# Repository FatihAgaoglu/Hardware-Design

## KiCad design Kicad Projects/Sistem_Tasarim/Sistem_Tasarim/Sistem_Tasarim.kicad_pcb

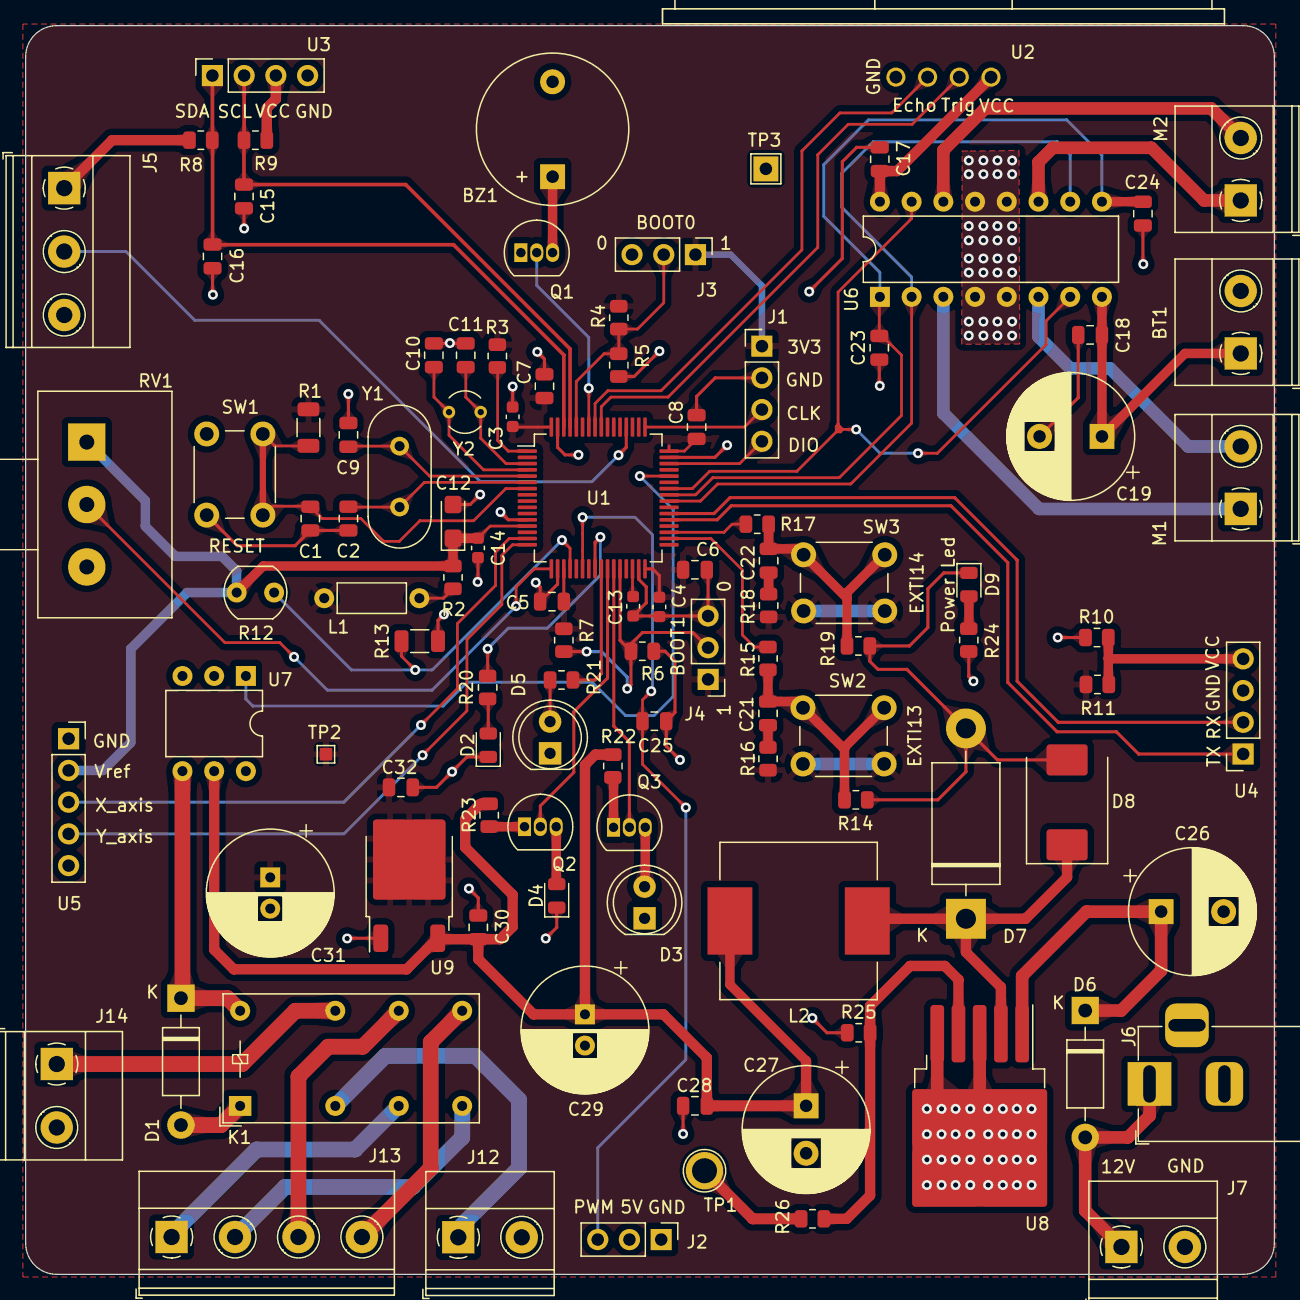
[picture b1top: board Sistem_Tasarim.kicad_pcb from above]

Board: 4 copper layers, 100.0 x 100.0 mm, 104 parts (0 on the bottom side), 68 nets.

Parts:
BT1: Battery; TerminalBlock_Phoenix_MKDS-1,5-2_1x02_P5.00mm_Horizontal
BZ1: Buzzer; Buzzer_12x9.5RM7.6
C1, C5, C6, C7, C8, C15, C16, C17, C18, C21, C22, C23, C24, C25, C28: 100nF; C_0805_2012Metric
C2, C9: 22pF; C_0805_2012Metric
C3, C4, C14: 100nF; C_0603_1608Metric
C10, C11: 6.8pF; C_0805_2012Metric
C12: 1uF; CP_EIA-3216-18_Kemet-A
C13: 2.2uF; C_0603_1608Metric
C19: 1000uF; CP_Radial_D10.0mm_P5.00mm
C26: 680uF; CP_Radial_D10.0mm_P5.00mm
C27: 220uF; CP_Radial_D10.0mm_P3.80mm
C29, C31: 10uF; CP_Radial_D10.0mm_P2.50mm
C30, C32: 1uF; C_0805_2012Metric
D1, D6: 1N4007; D_DO-41_SOD81_P10.16mm_Horizontal
D2, D4, D9: LED; LED_0805_2012Metric
D3, D5: LED; LED_D5.0mm
D7: 1N5822; D_DO-201AD_P15.24mm_Horizontal
D8: SS34; D_SMC
J1: Prog_Conn_01x04; PinHeader_1x04_P2.54mm_Vertical
J2, J3, J4: Conn_01x03; PinHeader_1x03_P2.54mm_Vertical
J5: Screw_Terminal_01x03; TerminalBlock_Phoenix_MKDS-1,5-3-5.08_1x03_P5.08mm_Horizont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
J6: Barrel_Jack_Switch_Pin3Ring; DC_Power_Jack
J7, J12, J14: Screw_Terminal_01x02; TerminalBlock_Phoenix_MKDS-1,5-2-5.08_1x02_P5.08mm_Horizont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
J13: Screw_Terminal_01x04; TerminalBlock_Phoenix_MKDS-1,5-4-5.08_1x04_P5.08mm_Horizont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
K1: AZ850-x; Relay_DPDT_Finder_30.22
L1: 100uH; L_Axial_L5.3mm_D2.2mm_P7.62mm_Horizontal_Vishay_IM-1
L2: 33uH; INDUCTOR_12x12x8
M1: Motor_DC_UST; TerminalBlock_Phoenix_MKDS-1,5-2_1x02_P5.00mm_Horizontal
M2: Motor_DC_ALT; TerminalBlock_Phoenix_MKDS-1,5-2_1x02_P5.00mm_Horizontal
Q1, Q2, Q3: BC547; TO-92_Inline
R1: 1K; R_1206_3216Metric
R2: 47R; R_0805_2012Metric
R3, R10, R11: 0R; R_0805_2012Metric
R4, R7: 10k; R_0805_2012Metric
R5, R6: 510R; R_0805_2012Metric
R8, R9: 4.7K; R_0805_2012Metric
R12: LDR03; R_LDR_5.0x4.1mm_P3mm_Vertical
R13: 10K; R_1206_3216Metric
R14, R19: 220K; R_0805_2012Metric
R15, R17: 330R; R_0805_2012Metric
R16, R18, R20, R21, R22, R23: 100R; R_0805_2012Metric
R24: 470R; R_0805_2012Metric
R25: 1K; R_0805_2012Metric
R26: 3K; R_0805_2012Metric
RV1: 100K; Potansiyometre
SW1, SW2, SW3: SW_MEC_5E; SW_PUSH_6mm_H4.3mm
TP1: 5V; TestPoint_Plated_Hole_D2.0mm
TP2: 3V3; TestPoint_Pad_1.0x1.0mm
TP3: GND; TestPoint_THTPad_2.0x2.0mm_Drill1.0mm
U1: STM32F401RCTx; LQFP-64_10x10mm_P0.5mm
U2: HC-SR04
U3: Oled_Display
U4: HC06 Bluetooth Sensor; HC06
U5: Joystick
U6: L293D; DIP-16_W7.62mm
U7: 4N25; DIP-6_W7.62mm
U8: LM2596S-5; TO-263-5_TabPin3
U9: LD1086DT33TR; TO-252-2
Y1: Crystal_8Mhz; Crystal_HC49-4H_Vertical
Y2: Crystal_32.768Khz; Crystal_AT310_D3.0mm_L10.0mm_Vertical

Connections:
+3V3: C3.1, C4.1, C5.1, C6.1, C7.1, C8.1, C31.1, C32.1, J1.1, J3.1, J4.1, L1.1, R1.1, R3.1, R4.1, R7.1, R11.2, R16.2, R18.2, SW2.1, SW2.2, SW3.1, SW3.2, TP2.1, U1.19 (VDD), U1.32 (VDD), U1.48 (VDD), U1.64 (VDD), U9.2 (OUT)
+5V: C17.2, C27.1, C28.1, C29.1, C30.1, J2.2, J5.1, L2.2, Q1.1 (C), R8.1, R9.1, R10.2, R22.1, R23.1, R24.1, R26.2, TP1.1, U2.1 (VCC), U3.3 (VCC), U6.16 (VCC1), U7.5, U9.3 (IN)
BOOT0: J3.2, R4.2, R5.1, U1.60 (BOOT0)
BOOT1: J4.2, R6.1, R7.2, U1.28 (PB2)
Buzzer_Output: Q1.2 (B), U1.58 (PB6)
DC_Engine_Left: U1.40 (PC9), U6.2 (1A), U6.10 (3A)
DC_Engine_PWM: C23.2, C24.2, U1.41 (PA8), U6.1 (EN1,2), U6.9 (EN3,4)
DC_Engine_Right: U1.42 (PA9), U6.7 (2A), U6.15 (4A)
Echo: U1.57 (PB5), U2.3 (ECHO)
GNDREF: BT1.2 (-), BZ1.2 (+), C1.1, C2.2, C3.2, C4.2, C5.2, C6.2, C7.2, C8.2, C9.2, C10.2, C11.2, C12.2, C13.1, C14.2, C15.2, C16.2, C17.1, C18.2, C19.2, C23.1, C24.1, C25.1, C26.2, C27.2, C28.2, C29.2, C30.2, C31.2, C32.2, D1.2 (A), D2.1 (K), D3.1 (K), D4.1 (K), D5.1 (K), D7.2 (A), D8.2 (A), D9.1 (K), J1.2, J2.1, J3.3, J4.3, J5.3, J6.2, J6.3, J7.2, K1.10, R5.2, R6.2, R13.2, R14.2, R19.2, R25.1, RV1.3, SW1.3 (K), SW1.4 (A), TP3.1, U1.12 (VSSA), U1.18 (VSS), U1.31 (VSS), U1.47 (VSS), U1.63 (VSS), U2.4 (GND), U3.4 (GND), U4.3 (GND), U5.1 (GND), U6.4 (GND), U6.5 (GND), U6.12 (GND), U6.13 (GND), U7.2, U8.3 (GND), U8.5 (~ON/OFF), U9.1 (ADJ/GND)
I2C_SCL: C15.1, R9.2, U1.61 (PB8), U3.2 (SCL)
I2C_SDA: C16.1, R8.2, U1.62 (PB9), U3.1 (SDA)
Interrupt_EXTI13: R15.1, U1.34 (PB13)
Interrupt_EXTI14: R17.1, U1.35 (PB14)
NRST: C1.2, R1.2, SW1.1, SW1.2, U1.7 (NRST)
unnamed: C26.1, D6.1 (K), U8.1 (VIN)
unnamed: R3.2, U1.1 (VBAT)
unnamed: R10.1, R11.1, U4.4 (VCC)
unnamed: BT1.1 (+), C18.1, C19.1, U6.8 (VCC2)
unnamed: BZ1.1 (-), Q1.3 (E)
unnamed: C21.2, R16.1
unnamed: C22.2, R18.1
unnamed: D1.1 (K), K1.1, U7.4
unnamed: D2.2 (A), R20.2
unnamed: D3.2 (A), Q3.3 (E)
unnamed: D4.2 (A), Q2.3 (E)
unnamed: D5.2 (A), R21.2
unnamed: D6.2 (A), J6.1, J7.1
unnamed: D7.1 (K), D8.1 (K), L2.1, U8.2 (OUT)
unnamed: D9.2 (A), R24.2
unnamed: J12.1, K1.3
unnamed: J13.1, K1.2
unnamed: J13.2, K1.4
unnamed: J13.3, K1.9
unnamed: J13.4, K1.7
unnamed: J14.1, K1.8
unnamed: L1.2, R2.1
unnamed: M1.1 (+), U6.3 (1Y)
unnamed: M1.2 (-), U6.6 (2Y)
unnamed: M2.1 (+), U6.11 (3Y)
unnamed: M2.2 (-), U6.14 (4Y)
unnamed: Q2.1 (C), R23.2
unnamed: Q3.1 (C), R22.2
unnamed: C21.1, R14.1, R15.2, SW2.3 (K), SW2.4 (A)
unnamed: C22.1, R17.2, R19.1, SW3.3 (K), SW3.4 (A)
unnamed: C13.2, U1.30 (VCAP1)
unnamed: R25.2, R26.1, U8.4 (FB)
PHOTO_ELECTRIC_SWITCH: J5.2, U1.52 (PC11)
RCC_OSC_HSE_1: C9.1, U1.5 (PH0), Y1.1
RCC_OSC_HSE_2: C2.1, U1.6 (PH1), Y1.2
RCC_OSC_LSE_1: C11.1, U1.3 (PC14), Y2.1
RCC_OSC_LSE_2: C10.1, U1.4 (PC15), Y2.2
Relay_Output: U1.44 (PA11), U7.1
SWCLK: J1.3, U1.49 (PA14)
SWDIO: J1.4, U1.46 (PA13)
Servo_Engine_PWM: C25.2, J2.3, U1.22 (PA6)
Trig: U1.56 (PB4), U2.2 (TRIG)
USART6_RX: U1.38 (PC7), U4.2 (TX)
USART6_TX: U1.37 (PC6), U4.1 (RX)
User_Led_0: R20.1, U1.24 (PC4)
User_Led_1: R21.1, U1.25 (PC5)
User_Led_2: Q2.2 (B), U1.26 (PB0)
User_Led_3: Q3.2 (B), U1.27 (PB1)
VREF+: C12.1, C14.1, R2.2, R12.1, RV1.1, U1.13 (VREF+), U5.2 (5V)
X_axis: U1.15 (PA1), U5.3 (VRX)
Y_axis: U1.16 (PA2), U5.4 (VRY)
ldr_value: R12.2, R13.1, U1.20 (PA4)
pot_value: RV1.2, U1.17 (PA3)

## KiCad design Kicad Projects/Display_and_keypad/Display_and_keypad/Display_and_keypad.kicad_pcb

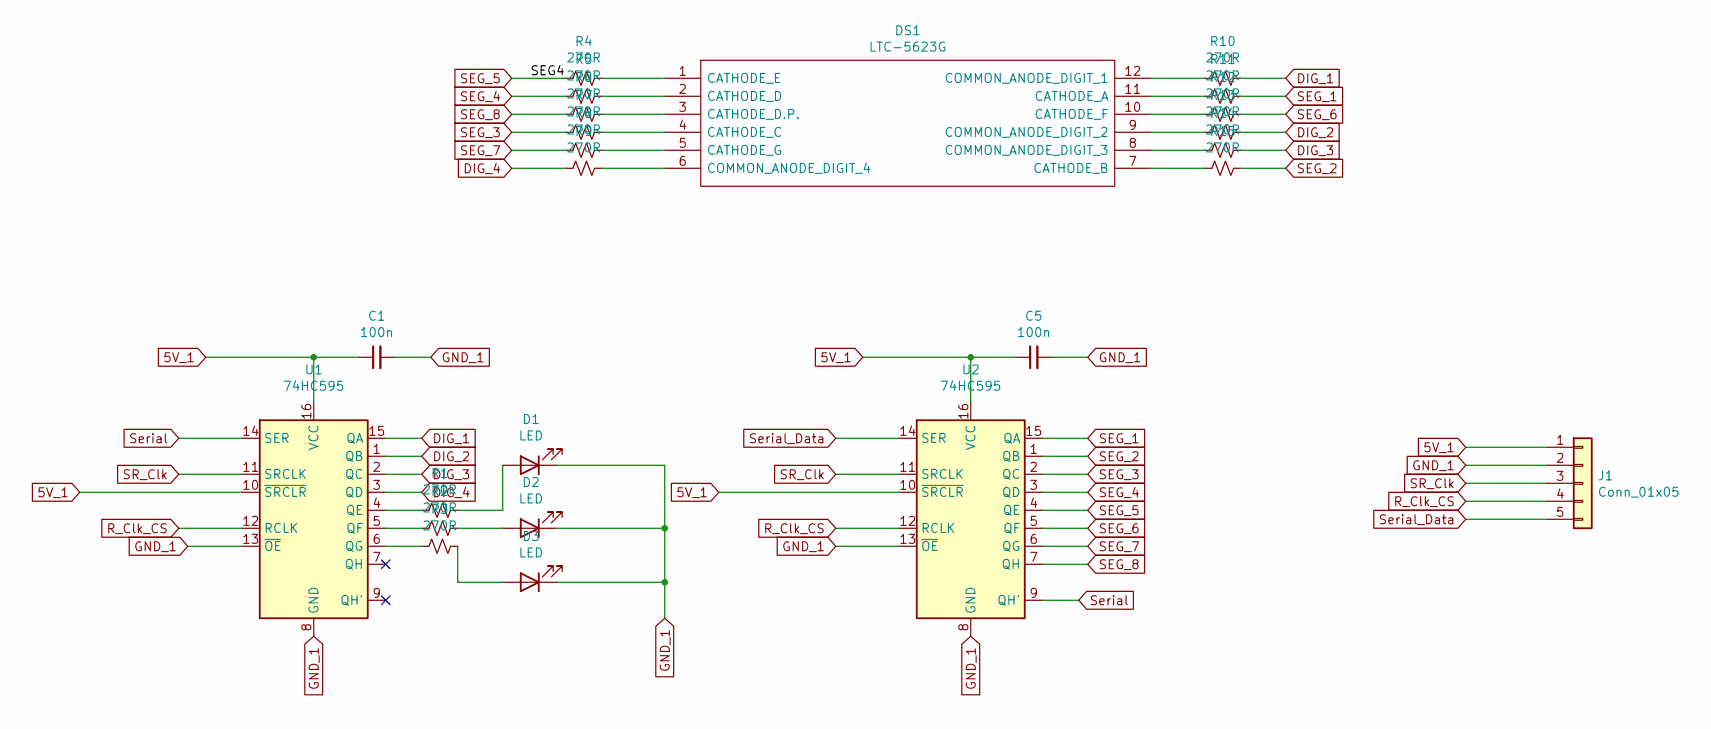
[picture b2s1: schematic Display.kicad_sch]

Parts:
C1, C5: 100n; C_0805_2012Metric_Pad1.18x1.45mm_HandSolder
D1, D2, D3: LED; LED_0805_2012Metric_Pad1.15x1.40mm_HandSolder
DS1: LTC-5623G; DIPS1524W75P254L5030H825Q12N
J1: Conn_01x05; PinHeader_1x05_P2.54mm_Vertical
R1, R2, R3, R4, R5, R6, R7, R8, R9, R10, R11, R12, R13, R14, R15: 270R; R_0805_2012Metric_Pad1.20x1.40mm_HandSolder
U1, U2: 74HC595; TSSOP-16_4.4x5mm_P0.65mm

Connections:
5V_1: C1.1, C5.1, J1.1, U1.10 (~SRCLR), U1.16 (VCC), U2.10 (~SRCLR), U2.16 (VCC)
DIG_1: R10.1, U1.15 (QA)
DIG_2: R13.1, U1.1 (QB)
DIG_3: R14.1, U1.2 (QC)
DIG_4: R9.2, U1.3 (QD)
GND_1: C1.2, C5.2, D1.1 (K), D2.1 (K), D3.1 (K), J1.2, U1.8 (GND), U1.13 (~OE), U2.8 (GND), U2.13 (~OE)
unnamed: D1.2 (A), R1.1
unnamed: D2.2 (A), R2.1
unnamed: D3.2 (A), R3.1
unnamed: DS1.1 (CATHODE_E), R4.1
unnamed: DS1.2 (CATHODE_D), R5.1
unnamed: DS1.3 (CATHODE_D.P.), R6.1
unnamed: DS1.4 (CATHODE_C), R7.1
unnamed: DS1.5 (CATHODE_G), R8.1
unnamed: DS1.6 (COMMON_ANODE_DIGIT_4), R9.1
unnamed: DS1.7 (CATHODE_B), R15.2
unnamed: DS1.8 (COMMON_ANODE_DIGIT_3), R14.2
unnamed: DS1.9 (COMMON_ANODE_DIGIT_2), R13.2
unnamed: DS1.10 (CATHODE_F), R12.2
unnamed: DS1.11 (CATHODE_A), R11.2
unnamed: DS1.12 (COMMON_ANODE_DIGIT_1), R10.2
unnamed: R1.2, U1.4 (QE)
unnamed: R2.2, U1.5 (QF)
unnamed: R3.2, U1.6 (QG)
R_Clk_CS: J1.4, U1.12 (RCLK), U2.12 (RCLK)
SEG_1: R11.1, U2.15 (QA)
SEG_2: R15.1, U2.1 (QB)
SEG_3: R7.2, U2.2 (QC)
SEG_4: R5.2, U2.3 (QD)
SEG_5: R4.2, U2.4 (QE)
SEG_6: R12.1, U2.5 (QF)
SEG_7: R8.2, U2.6 (QG)
SEG_8: R6.2, U2.7 (QH)
SR_Clk: J1.3, U1.11 (SRCLK), U2.11 (SRCLK)
Serial: U1.14 (SER), U2.9 (QH')
Serial_Data: J1.5, U2.14 (SER)

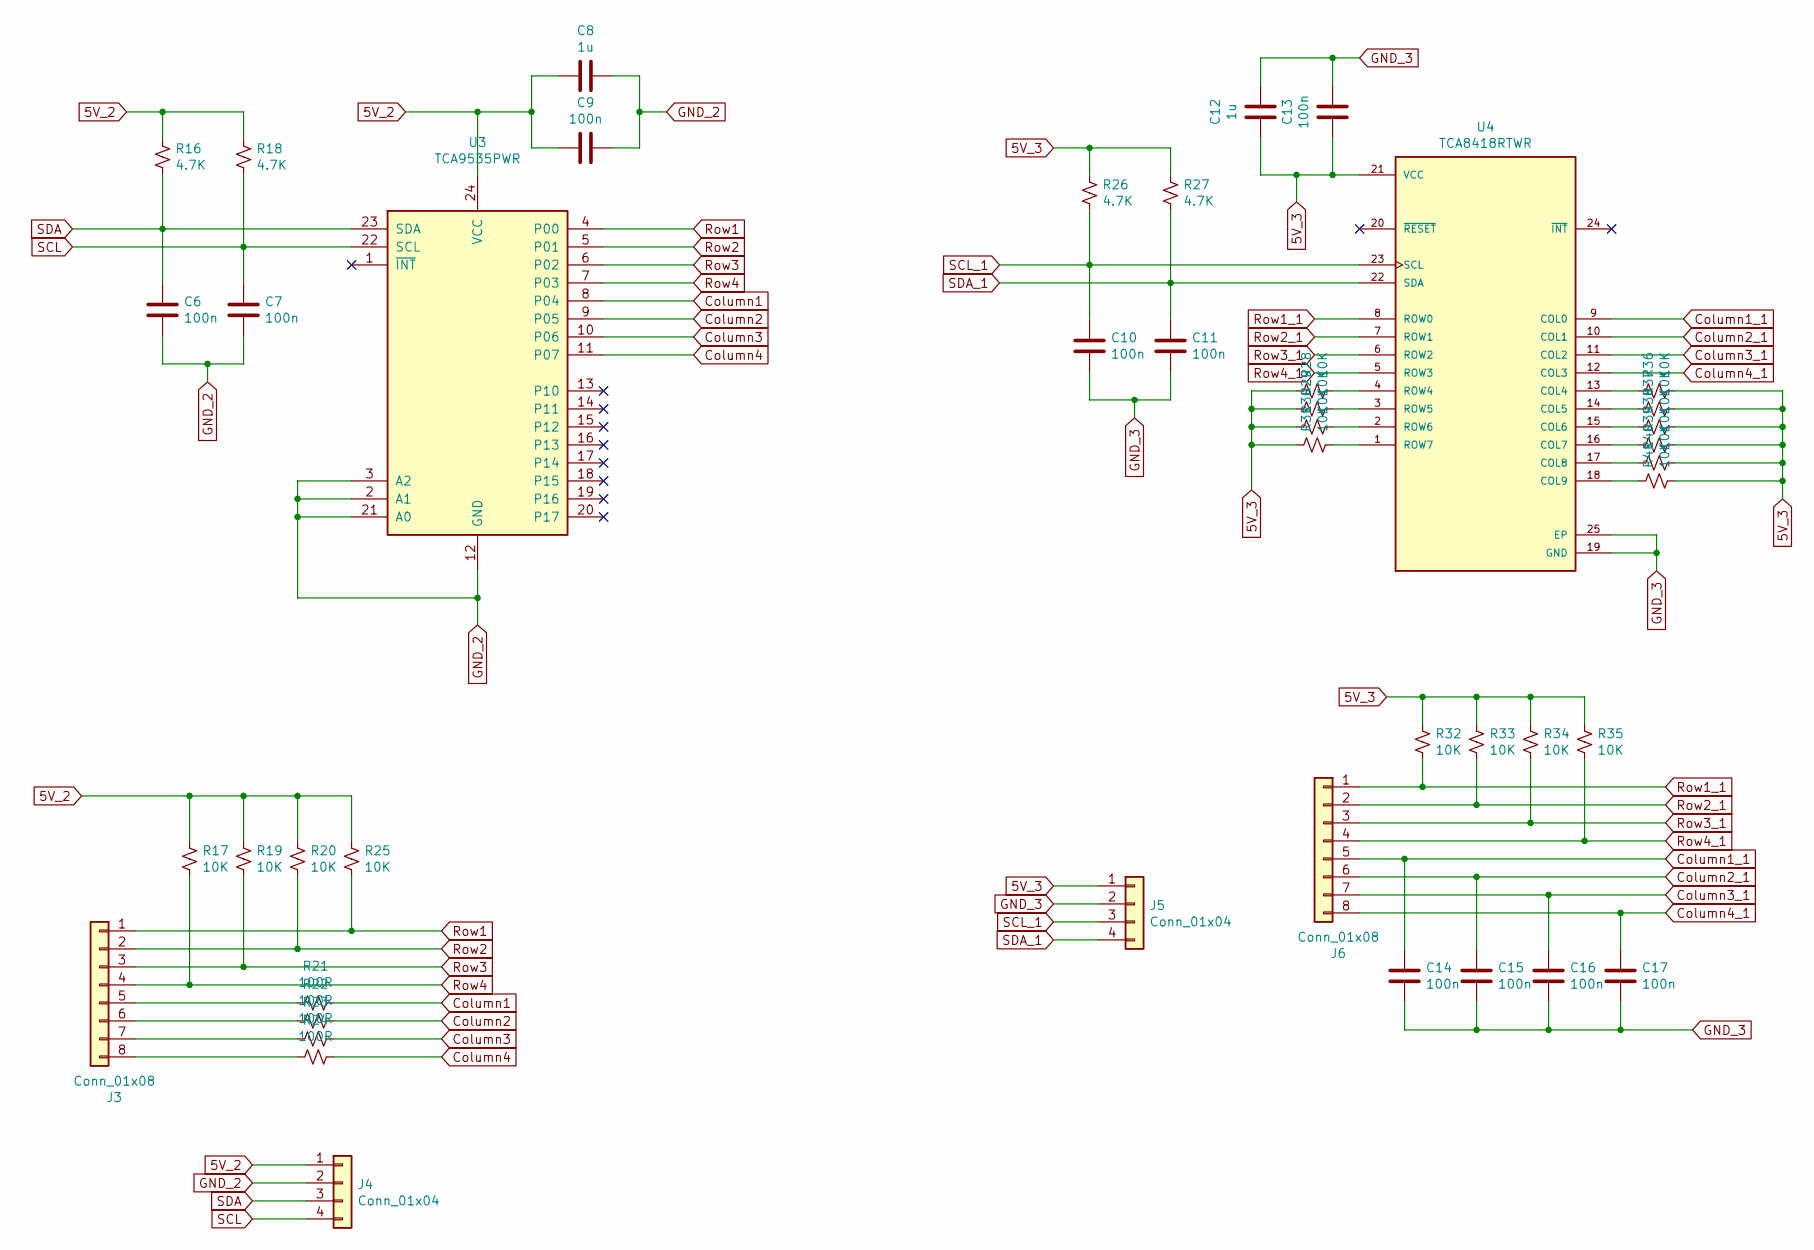
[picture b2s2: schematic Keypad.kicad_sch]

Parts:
C6, C7, C9, C10, C11, C13, C14, C15, C16, C17: 100n; C_0805_2012Metric_Pad1.18x1.45mm_HandSolder
C8, C12: 1u; C_0805_2012Metric_Pad1.18x1.45mm_HandSolder
J3, J6: Conn_01x08; PinHeader_1x08_P2.54mm_Vertical
J4, J5: Conn_01x04; PinHeader_1x04_P2.54mm_Vertical
R16, R18, R26, R27: 4.7K; R_0805_2012Metric_Pad1.20x1.40mm_HandSolder
R17, R19, R20, R25, R28, R29, R30, R31, R32, R33, R34, R35, R36, R37, R38, R39, R40, R41: 10K; R_0805_2012Metric_Pad1.20x1.40mm_HandSolder
R21, R22, R23, R24: 100R; R_0805_2012Metric_Pad1.20x1.40mm_HandSolder
U3: TCA9535PWR; TSSOP-24_4.4x7.8mm_P0.65mm
U4: TCA8418RTWR; QFN50P400X400X80-25N

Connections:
5V_2: C8.2, C9.2, J4.1, R16.1, R17.1, R18.1, R19.1, R20.1, R25.1, U3.24 (VCC)
5V_3: C12.2, C13.2, J5.1, R26.1, R27.1, R28.1, R29.1, R30.1, R31.1, R32.1, R33.1, R34.1, R35.1, R36.2, R37.2, R38.2, R39.2, R40.2, R41.2, U4.21 (VCC)
Column1: R21.1, U3.8 (P04)
Column1_1: C14.1, J6.5, U4.9 (COL0)
Column2: R22.1, U3.9 (P05)
Column2_1: C15.1, J6.6, U4.10 (COL1)
Column3: R23.1, U3.10 (P06)
Column3_1: C16.1, J6.7, U4.11 (COL2)
Column4: R24.1, U3.11 (P07)
Column4_1: C17.1, J6.8, U4.12 (COL3)
GND_2: C6.2, C7.2, C8.1, C9.1, J4.2, U3.2 (A1), U3.3 (A2), U3.12 (GND), U3.21 (A0)
GND_3: C10.2, C11.2, C12.1, C13.1, C14.2, C15.2, C16.2, C17.2, J5.2, U4.19 (GND), U4.25 (EP)
unnamed: J3.5, R21.2
unnamed: J3.6, R22.2
unnamed: J3.7, R23.2
unnamed: J3.8, R24.2
unnamed: R28.2, U4.4 (ROW4)
unnamed: R29.2, U4.3 (ROW5)
unnamed: R30.2, U4.2 (ROW6)
unnamed: R31.2, U4.1 (ROW7)
unnamed: R36.1, U4.13 (COL4)
unnamed: R37.1, U4.14 (COL5)
unnamed: R38.1, U4.15 (COL6)
unnamed: R39.1, U4.16 (COL7)
unnamed: R40.1, U4.17 (COL8)
unnamed: R41.1, U4.18 (COL9)
Row1: J3.1, R25.2, U3.4 (P00)
Row1_1: J6.1, R32.2, U4.8 (ROW0)
Row2: J3.2, R20.2, U3.5 (P01)
Row2_1: J6.2, R33.2, U4.7 (ROW1)
Row3: J3.3, R19.2, U3.6 (P02)
Row3_1: J6.3, R34.2, U4.6 (ROW2)
Row4: J3.4, R17.2, U3.7 (P03)
Row4_1: J6.4, R35.2, U4.5 (ROW3)
SCL: C7.1, J4.4, R18.2, U3.22 (SCL)
SCL_1: C10.1, J5.3, R26.2, U4.23 (SCL)
SDA: C6.1, J4.3, R16.2, U3.23 (SDA)
SDA_1: C11.1, J5.4, R27.2, U4.22 (SDA)

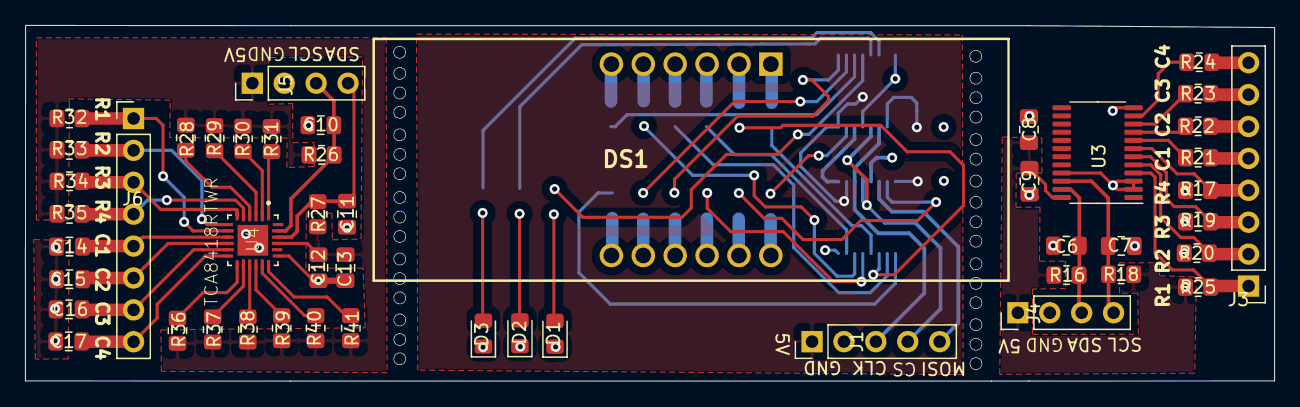
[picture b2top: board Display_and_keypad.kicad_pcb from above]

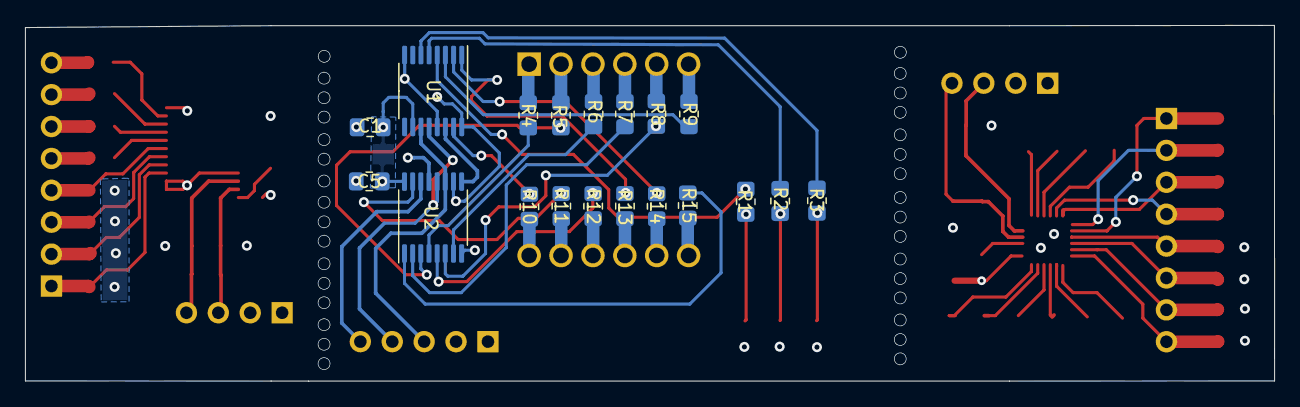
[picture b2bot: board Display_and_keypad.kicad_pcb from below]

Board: 4 copper layers, 99.5 x 28.3 mm, 68 parts (19 on the bottom side), 74 nets.

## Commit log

2023-04-22 Kicad Projects
2023-04-22 Display_and_Keypad_Board
2023-04-22 Sistem_Tasarim_Board
2023-06-30 Motion Detector Project
2023-06-30 Gerekli
2023-06-30 Altium Projects
2023-06-30 Deneme
2023-06-30 Altium Designer Projects
2023-06-30 Motion Detector PCB
2023-06-30 Sistem Tasarım
    Sistem Tasarım
